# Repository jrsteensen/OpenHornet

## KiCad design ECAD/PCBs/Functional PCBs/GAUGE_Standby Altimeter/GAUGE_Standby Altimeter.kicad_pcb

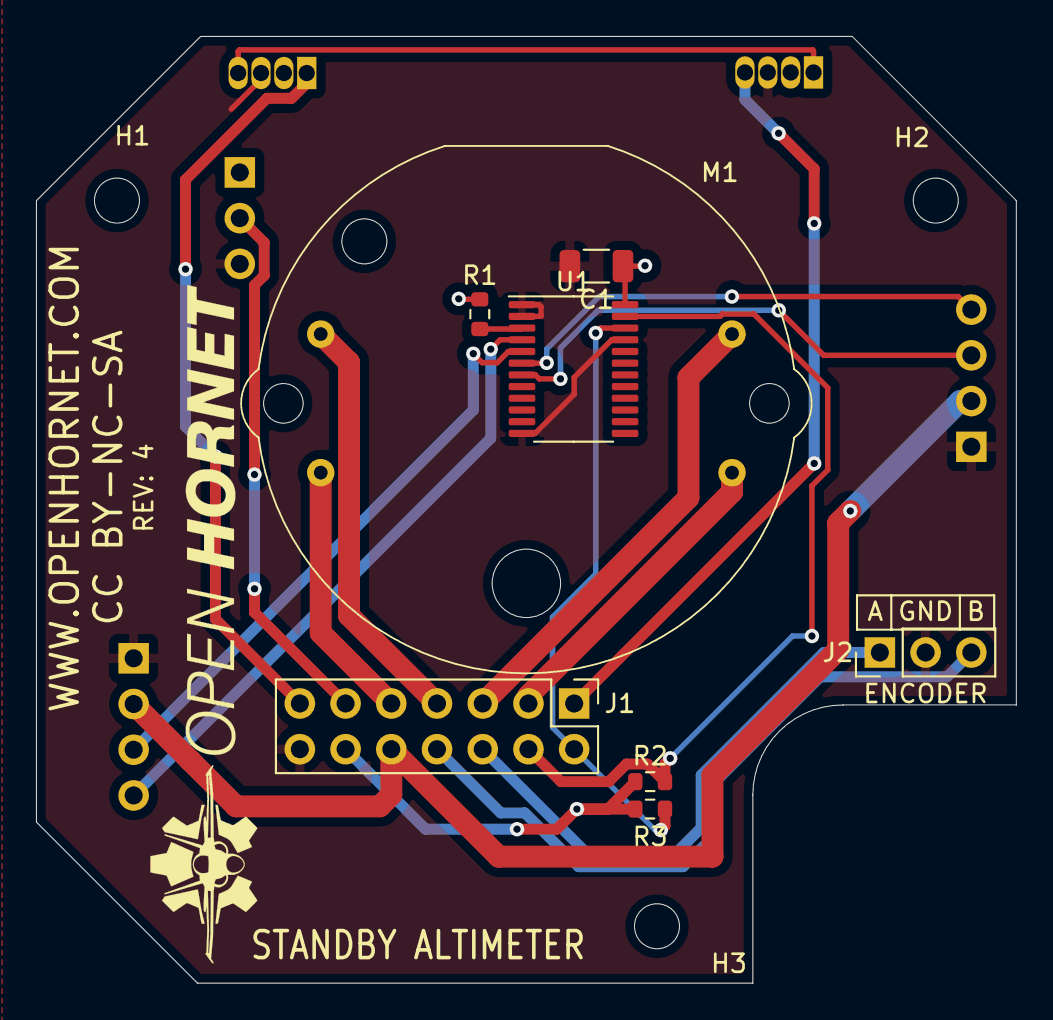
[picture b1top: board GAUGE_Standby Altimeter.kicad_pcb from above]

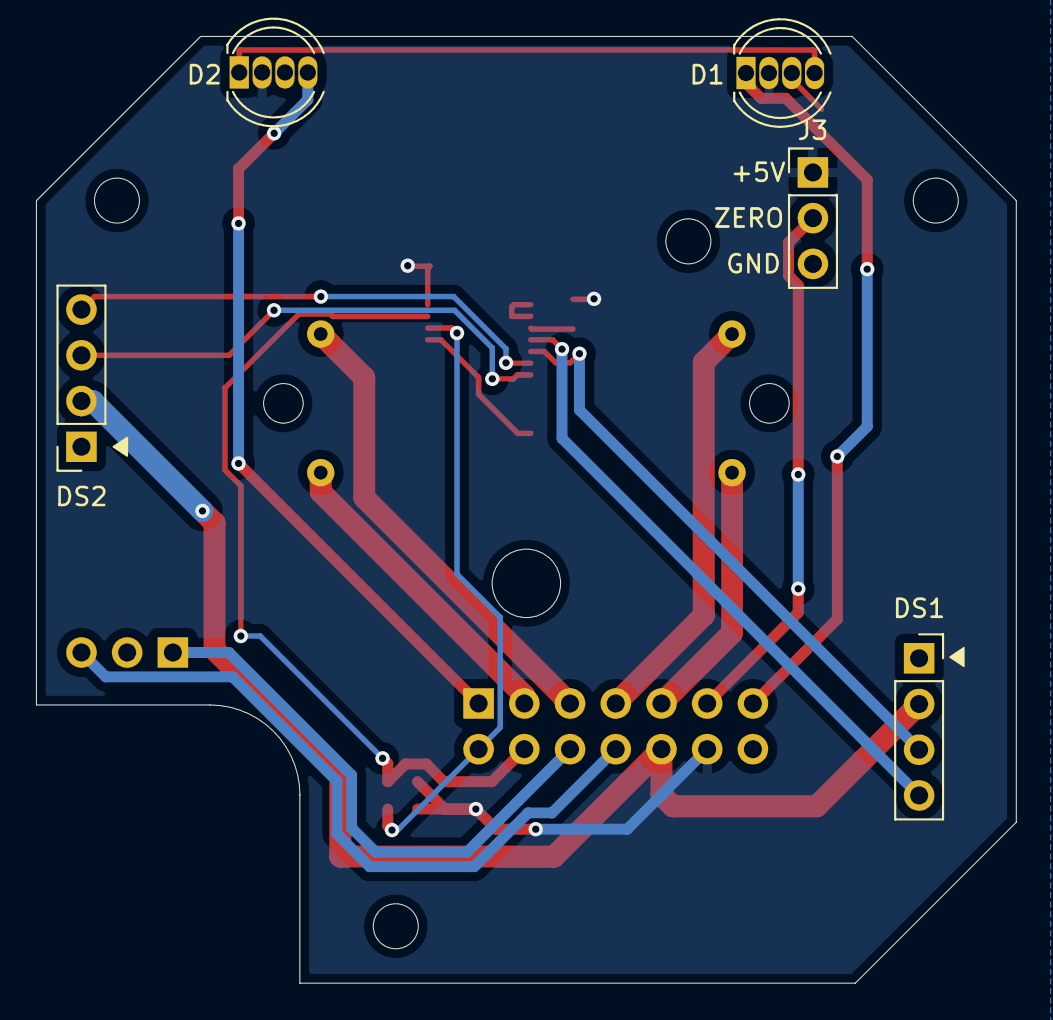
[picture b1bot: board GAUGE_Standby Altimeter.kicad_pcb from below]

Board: 2 copper layers, 54.4 x 52.6 mm, 16 parts (5 on the bottom side), 20 nets.

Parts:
C1: 47uF; C_1206_3216Metric
D1, D2: 1938; LED_D5.0mm-4_RGB
DS1: 10K_ALT_DISP; PinSocket_1x04_P2.54mm_Vertical
DS2: PRESS_DISP; PinSocket_1x04_P2.54mm_Vertical
H1, H2, H3: MountingHole; MountingHole_2.5mm
J1: ALT_CONN; PinHeader_2x07_P2.54mm_Vertical
J2: ENCODER; PinHeader_1x03_P2.54mm_Vertical
J3: ZERO; PinHeader_1x03_P2.54mm_Vertical
M1: VID29-02
R1, R2, R3: 10K; R_0603_1608Metric
U1: TCA9548APWR; TSSOP-24_4.4x7.8mm_P0.65mm

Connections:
+3V3: DS1.2, DS2.2, J1.10
+5V: C1.1, D1.2, D2.2, J1.12, J3.1, R1.1, R2.1, R3.1, U1.24
/CH_A: J1.6, J2.1
/CH_B: J1.8, J2.3
/COIL1: J1.7, M1.1
/COIL2: J1.9, M1.2
/COIL3: J1.3, M1.3
/COIL4: J1.5, M1.4
/LED_DIN: D1.1, J1.13
/LED_DOUT: D2.4, J1.1
/SC0: DS1.3, U1.5
/SC1: DS2.3, U1.7
/SCL: J1.2, R3.2, U1.22
/SD0: DS1.4, U1.4
/SD1: DS2.4, U1.6
/SDA: J1.4, R2.2, U1.23
/ZERO_DETECT: J1.11, J3.2
GND: C1.2, D1.3, D2.3, DS1.1, DS2.1, J1.14, J2.2, J3.3, U1.1, U1.2, U1.12, U1.21
unnamed: D1.4, D2.1
unnamed: R1.2, U1.3

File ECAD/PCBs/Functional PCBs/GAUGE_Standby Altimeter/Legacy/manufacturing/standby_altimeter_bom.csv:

Comment,Designator,Footprint,LCSC
"47uF","C1","Capacitor_SMD:C_1206_3216Metric","C96123"
"1938","D1,D2","LED_THT:LED_D5.0mm-4_RGB",""
"10K_ALT_DISP","DS1","Connector_PinSocket_2.54mm:PinSocket_1x04_P2.54mm_Vertical",""
"PRESS_DISP","DS2","Connector_PinSocket_2.54mm:PinSocket_1x04_P2.54mm_Vertical",""
"MountingHole","H1,H2,H3","MountingHole:MountingHole_2.5mm",""
"ALT_CONN","J1","Connector_PinHeader_2.54mm:PinHeader_2x07_P2.54mm_Vertical",""
"ENCODER","J2","Connector_PinHeader_2.54mm:PinHeader_1x03_P2.54mm_Vertical",""
"ZERO","J3","Connector_PinHeader_2.54mm:PinHeader_1x03_P2.54mm_Vertical",""
"VID29-02","M1","KiCAD Libraries:VID29-02",""
"10K","R1,R2,R3","Resistor_SMD:R_0603_1608Metric","C25804"
"TCA9548APWR","U1","Package_SO:TSSOP-24_4.4x7.8mm_P0.65mm","C130026"

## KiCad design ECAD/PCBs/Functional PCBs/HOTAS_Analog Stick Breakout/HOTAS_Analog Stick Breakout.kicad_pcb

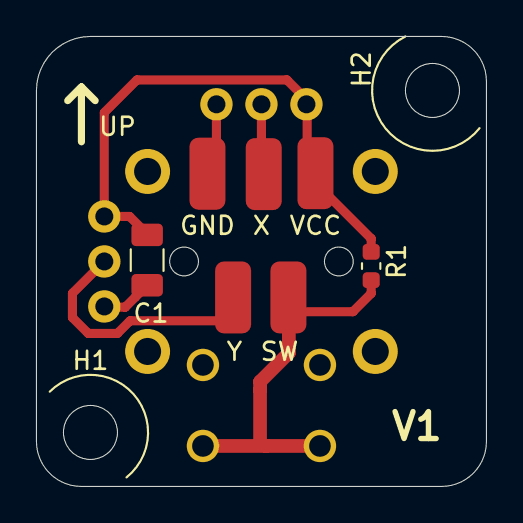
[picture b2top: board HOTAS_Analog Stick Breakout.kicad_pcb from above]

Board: 2 copper layers, 25.0 x 25.0 mm, 10 parts (1 on the bottom side), 5 nets.

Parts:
C1: 4.7uF; C_1206_3216Metric
H1, H2: MountingHole; MountingHole_3mm
J2, J3, J4, J5, J6: Conn_01x01; SolderWirePad_1x01_SMD_2x4mm
JOY1: ANALOGSTICK_CENTERPUSH; RKJXV12
R1: 10k; R_0603_1608Metric

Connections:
GND: C1.2, J6.1, JOY1.1, JOY1.4, JOY1.a, JOY1.c
unnamed: J3.1, JOY1.5
unnamed: J4.1, JOY1.2
unnamed: J5.1, JOY1.b, JOY1.d, R1.2
VCC: C1.1, J2.1, JOY1.3, JOY1.6, R1.1

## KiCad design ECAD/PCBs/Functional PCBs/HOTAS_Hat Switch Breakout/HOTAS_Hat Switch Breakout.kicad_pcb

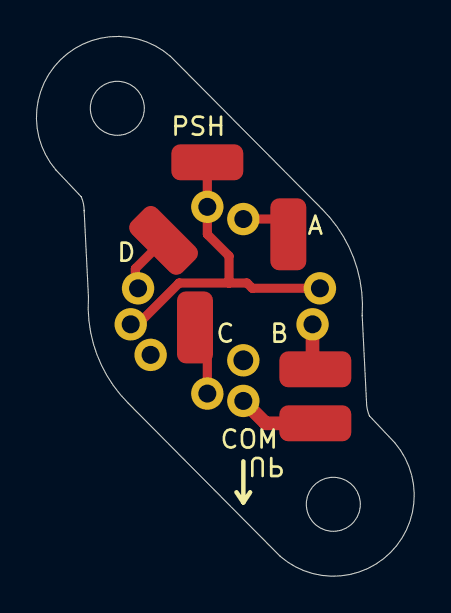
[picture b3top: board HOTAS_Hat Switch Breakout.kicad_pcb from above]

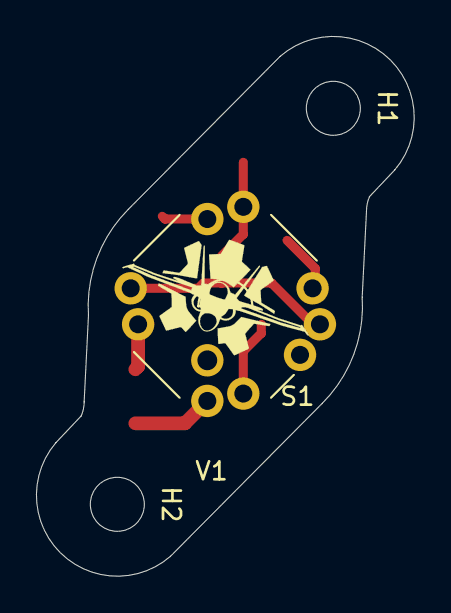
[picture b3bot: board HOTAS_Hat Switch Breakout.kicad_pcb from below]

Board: 2 copper layers, 21.0 x 30.0 mm, 9 parts (3 on the bottom side), 6 nets.

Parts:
H1, H2: MountingHole; MountingHole_3mm
J1, J2, J3, J4, J5, J6: Conn_01x01; SolderWirePad_1x01_SMD_2x4mm
S1: 8WayHat_CenterPush; RKJXM10

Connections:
unnamed: J1.1, S1.A
unnamed: J2.1, S1.B
unnamed: J3.1, S1.C
unnamed: J4.1, S1.D
unnamed: J5.1, S1.PUSH1, S1.PUSH2, S1.PUSH3
unnamed: J6.1, S1.COM

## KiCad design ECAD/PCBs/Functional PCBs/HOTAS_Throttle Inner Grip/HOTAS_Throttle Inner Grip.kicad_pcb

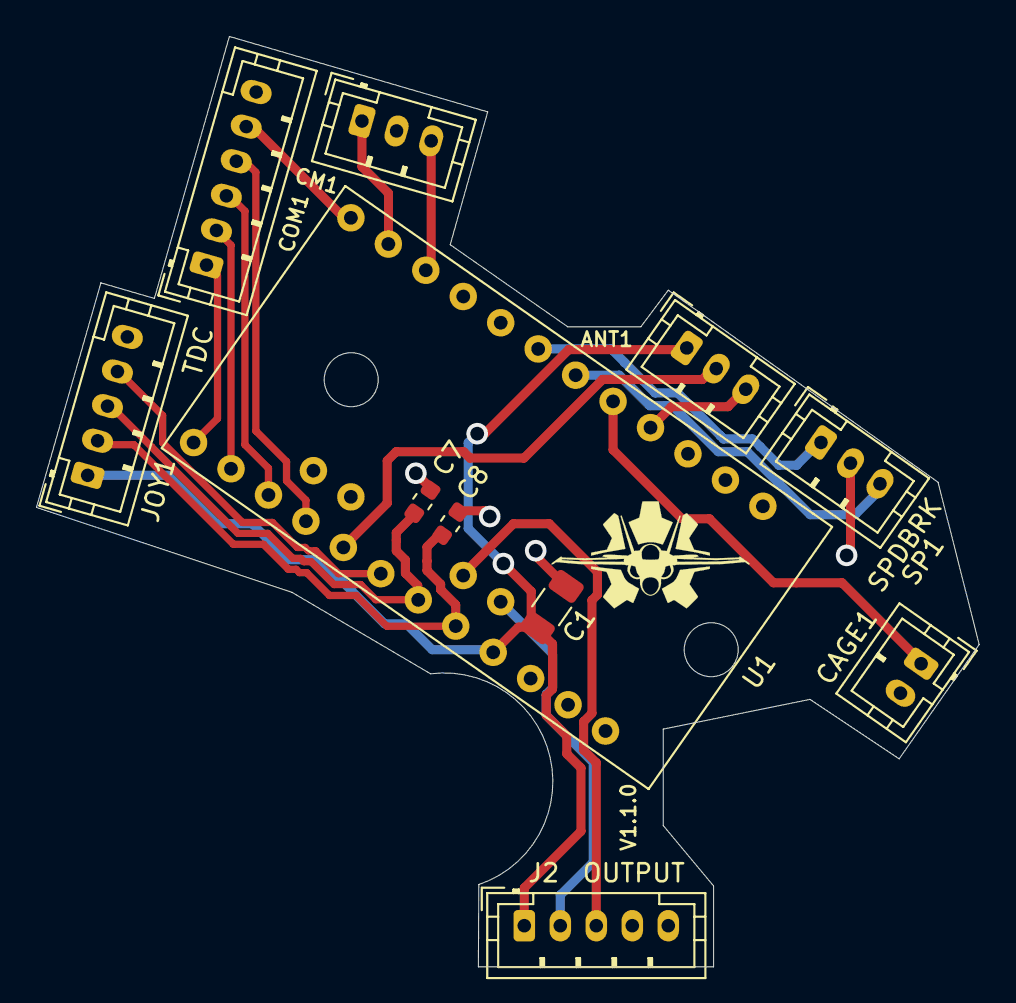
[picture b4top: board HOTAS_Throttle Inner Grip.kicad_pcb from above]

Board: 2 copper layers, 52.4 x 51.7 mm, 13 parts (0 on the bottom side), 18 nets.

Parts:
ANT1: Conn_01x03; JST_PH_B3B-PH-K_1x03_P2.00mm_Vertical
C1: 10uF; C_1206_3216Metric
C7, C8: 0.1uF; C_0603_1608Metric
CAGE1: Conn_01x02; JST_PH_B2B-PH-K_1x02_P2.00mm_Vertical
CM1: Conn_01x03; JST_PH_B3B-PH-K_1x03_P2.00mm_Vertical
COM1: COMS; JST_PH_B6B-PH-K_1x06_P2.00mm_Vertical
H1, H4: MountingHole; MountingHole_3mm
J2: OUTPUT; JST_PH_B5B-PH-K_1x05_P2.00mm_Vertical
JOY1: TDC; JST_PH_B5B-PH-K_1x05_P2.00mm_Vertical
SP1: SPDBRK; JST_PH_B3B-PH-K_1x03_P2.00mm_Vertical
U1: ProMini_NoProgrammingHeader; Arduino_Mini_Pro_No_Programming_Header

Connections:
/A: COM1.1, U1.13 (D10)
/ANTENNA_ELEVATION: ANT1.2, U1.17 (A0)
/B: COM1.2, U1.14 (D11)
/C: COM1.3, U1.15 (D12)
/CAGE-UNCAGE: CAGE1.1, U1.5 (D2)
/COUNTERMEASURES_AFT: CM1.3, U1.10 (D7)
/COUNTERMEASURES_FWD: CM1.1, U1.11 (D8)
/D: COM1.4, U1.16 (D13)
/I2C_DATA: J2.3, U1.33 (SDA)
/I2C_SCK: J2.2, U1.34 (SCL)
/JOY_SW: JOY1.4, U1.18 (A1)
/JOY_X: C8.1, JOY1.2, U1.20 (A3)
/JOY_Y: C7.1, JOY1.3, U1.19 (A2)
/PUSH: COM1.5, U1.12 (D9)
/SPEEDBREAK_EXTEND: SP1.1, U1.7 (D4)
/SPEEDBREAK_RETRACT: SP1.3, U1.6 (D3)
GND: ANT1.3, C1.2, C7.2, C8.2, CAGE1.2, CM1.2, COM1.6, J2.5, JOY1.5, SP1.2, U1.4 (GND), U1.23 (GND)
VCC: ANT1.1, C1.1, J2.1, JOY1.1, U1.21 (VCC)

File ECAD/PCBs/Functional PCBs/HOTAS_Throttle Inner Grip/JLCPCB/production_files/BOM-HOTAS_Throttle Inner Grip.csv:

Comment,Designator,Footprint,LCSC
Conn_01x02,CAGE1,JST_PH_B2B-PH-K_1x02_P2.00mm_Vertical,C131337
Conn_01x03,"ANT1,CM1,SP1",JST_PH_B3B-PH-K_1x03_P2.00mm_Vertical,C131339
COMS,COM1,JST_PH_B6B-PH-K_1x06_P2.00mm_Vertical,C131342
10uF,C1,C_1206_3216Metric,C13585
0.1uF,"C7,C8",C_0603_1608Metric,C14663
OUTPUT,"J2,JOY1",JST_PH_B5B-PH-K_1x05_P2.00mm_Vertical,C157993
ProMini_NoProgrammingHeader,U1,Arduino_Mini_Pro_No_Programming_Header,
MountingHole,H1,MountingHole_3mm,
MountingHole,H4,MountingHole_3mm,

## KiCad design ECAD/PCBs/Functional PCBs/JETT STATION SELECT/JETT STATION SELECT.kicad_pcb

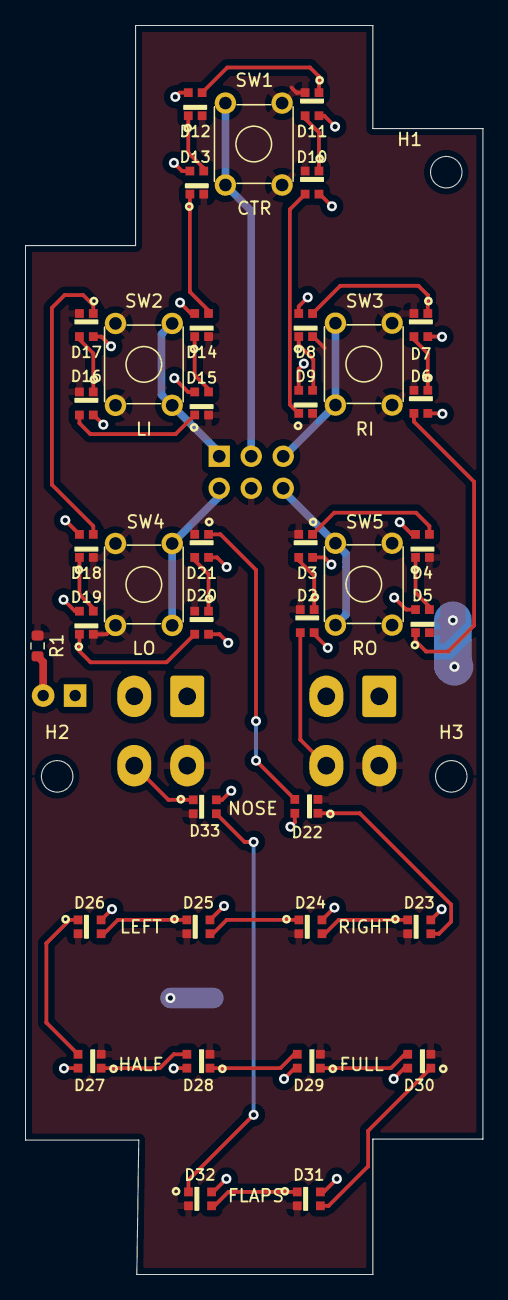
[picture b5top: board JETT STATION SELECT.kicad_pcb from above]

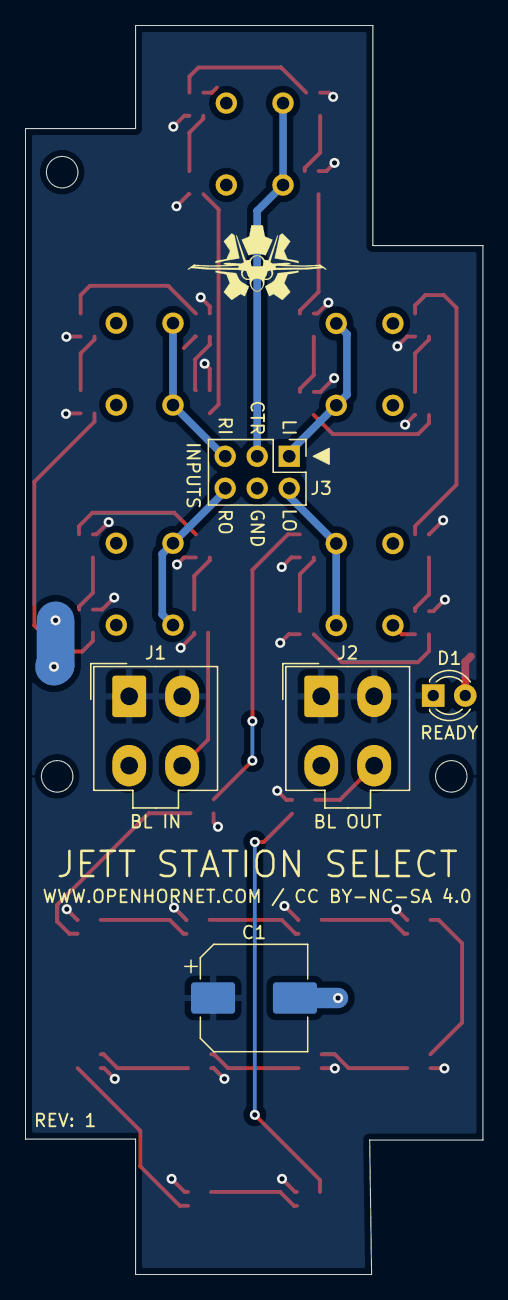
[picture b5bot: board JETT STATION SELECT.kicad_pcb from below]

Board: 2 copper layers, 36.3 x 99.1 mm, 47 parts (6 on the bottom side), 41 nets.

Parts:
C1: 1000 nF; CP_Elec_8x10
D1: READY; LED_D3.0mm
D2, D3, D4, D5, D6, D7, D8, D9, D10, D11, D12, D13, D14, D15, D16, D17, D18, D19, D20, D21, D22, D23, D24, D25, D26, D27, D28, D29, D30, D31, D32, D33: LED; WS2812-2020
H1, H2, H3: MountingHole; MountingHole_2.5mm
J1: BL IN; Molex_Mini-Fit_Jr_5566-04A_2x02_P4.20mm_Vertical
J2: BL OUT; Molex_Mini-Fit_Jr_5566-04A_2x02_P4.20mm_Vertical
J3: INPUTS; PinHeader_2x03_P2.54mm_Vertical
LOGO1: OpenHornetLogoSmall; OH_LOGO_ONLY_11x6mm
R1: R; R_0603_1608Metric
SW1: CTR; SW_TH_Tactile_Omron_B3F-10xx
SW2: LI; SW_TH_Tactile_Omron_B3F-10xx
SW3: RI; SW_TH_Tactile_Omron_B3F-10xx
SW4: LO; SW_TH_Tactile_Omron_B3F-10xx
SW5: RO; SW_TH_Tactile_Omron_B3F-10xx

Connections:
/BL_+5V: C1.1, D1.1, D2.4, D3.4, D4.4, D5.4, D6.4, D7.4, D8.4, D9.4, D10.4, D11.4, D12.4, D13.4, D14.4, D15.4, D16.4, D17.4, D18.4, D19.4, D20.4, D21.4, D22.4, D23.4, D24.4, D25.4, D26.4, D27.4, D28.4, D29.4, D30.4, D31.4, D32.4, D33.4, J1.1, J1.2, J2.1, J2.2
/BL_DATA1: D9.1, D10.3
/BL_DATA2: D17.1, D18.3
/BL_DATA3: D25.1, D26.3
/BL_DIN: D2.3, J1.4
/BL_DOUT: D33.1, J2.4
/CTR_SW: J3.3, SW1.1, SW1.2
/LI_SW: J3.1, SW2.1, SW2.2
/LO_SW: J3.2, SW4.1, SW4.2
/RI_SW: J3.5, SW3.1, SW3.2
/RO_SW: J3.6, SW5.1, SW5.2
GND: C1.2, D2.2, D3.2, D4.2, D5.2, D6.2, D7.2, D8.2, D9.2, D10.2, D11.2, D12.2, D13.2, D14.2, D15.2, D16.2, D17.2, D18.2, D19.2, D20.2, D21.2, D22.2, D23.2, D24.2, D25.2, D26.2, D27.2, D28.2, D29.2, D30.2, D31.2, D32.2, D33.2, J1.3, J2.3, J3.4, R1.2, SW1.3, SW1.4, SW2.3, SW2.4, SW3.3, SW3.4, SW4.3, SW4.4, SW5.3, SW5.4
unnamed: D1.2, R1.1
unnamed: D2.1, D3.3
unnamed: D3.1, D4.3
unnamed: D4.1, D5.3
unnamed: D5.1, D6.3
unnamed: D6.1, D7.3
unnamed: D7.1, D8.3
unnamed: D8.1, D9.3
unnamed: D10.1, D11.3
unnamed: D11.1, D12.3
unnamed: D12.1, D13.3
unnamed: D13.1, D14.3
unnamed: D14.1, D15.3
unnamed: D15.1, D16.3
unnamed: D16.1, D17.3
unnamed: D18.1, D19.3
unnamed: D19.1, D20.3
unnamed: D20.1, D21.3
unnamed: D21.1, D22.3
unnamed: D22.1, D23.3
unnamed: D23.1, D24.3
unnamed: D24.1, D25.3
unnamed: D26.1, D27.3
unnamed: D27.1, D28.3
unnamed: D28.1, D29.3
unnamed: D29.1, D30.3
unnamed: D30.1, D31.3
unnamed: D31.1, D32.3
unnamed: D32.1, D33.3

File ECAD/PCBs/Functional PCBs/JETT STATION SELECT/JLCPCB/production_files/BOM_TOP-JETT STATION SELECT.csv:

Comment,Designator,Footprint,LCSC
R,R1,R_0603_1608Metric,C23138
LED,"D10,D11,D12,D13,D14,D15,D16,D17,D18,D19,D2,D20,D21,D22,D23,D24,D25,D26,D27,D28,D29,D3,D30,D31,D32,D33,D4,D5,D6,D7,D8,D9",WS2812-2020,C965555
RO,SW5,SW_TH_Tactile_Omron_B3F-10xx,
LO,SW4,SW_TH_Tactile_Omron_B3F-10xx,
RI,SW3,SW_TH_Tactile_Omron_B3F-10xx,
LI,SW2,SW_TH_Tactile_Omron_B3F-10xx,
CTR,SW1,SW_TH_Tactile_Omron_B3F-10xx,

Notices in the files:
ECAD/PCBs/Functional PCBs/GAUGE_Standby Altimeter/GAUGE_Standby Altimeter.kicad_pcb:
CC BY-NC-SA
ECAD/PCBs/Functional PCBs/JETT STATION SELECT/JETT STATION SELECT.kicad_pcb:
WWW.OPENHORNET.COM / CC BY-NC-SA 4.0
